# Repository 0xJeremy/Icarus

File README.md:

# Icarus Power Distribution Board

### Board Layout

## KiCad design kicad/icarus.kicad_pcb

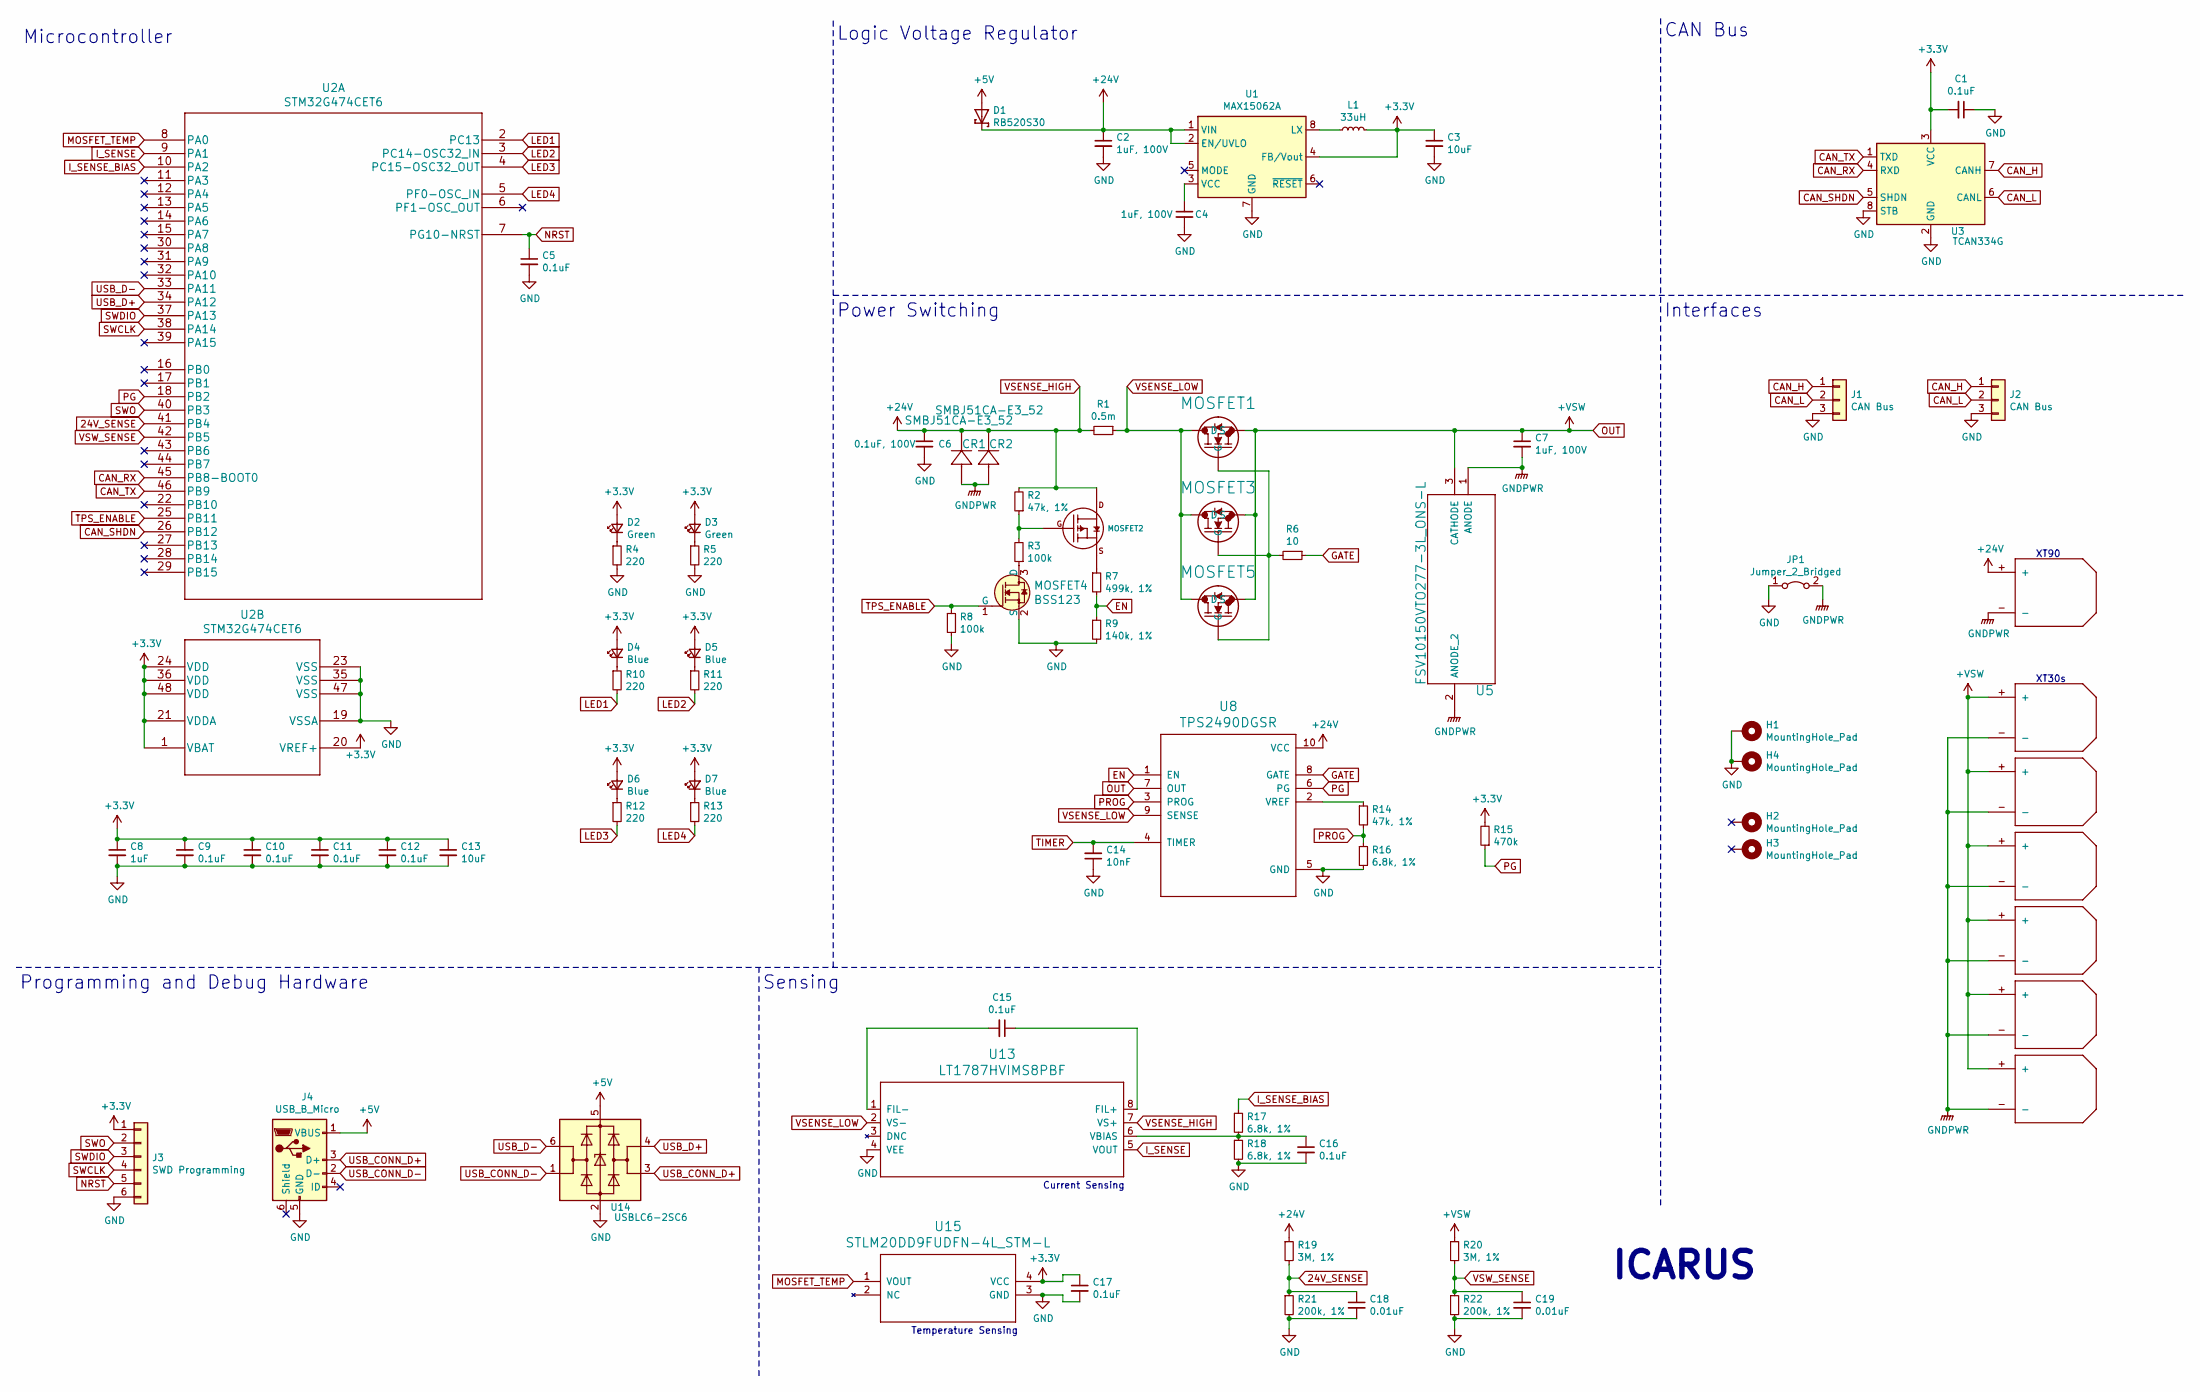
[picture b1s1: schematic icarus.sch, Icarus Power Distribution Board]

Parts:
C1, C5, C9, C10, C11, C12, C15, C16, C17: 0.1uF; C_0402_1005Metric
C2, C4, C7: 1uF, 100V; C_0805_2012Metric
C3, C13: 10uF; C_0402_1005Metric
C6: 0.1uF, 100V; C_0402_1005Metric
C8: 1uF; C_0402_1005Metric
C14: 10nF; C_0402_1005Metric
C18, C19: 0.01uF; C_0402_1005Metric
CR1, CR2: SMBJ51CA-E3_52; SMBJ51CA-E3-52
D1: RB520S30
D2, D3: Green; LED_0603_1608Metric
D4, D5, D6, D7: Blue; LED_0603_1608Metric
H1, H2, H3, H4: MountingHole_Pad; MountingHole_2.7mm_M2.5_DIN965_Pad
J1, J2: CAN Bus; JST_PH_B3B-PH-K_1x03_P2.00mm_Vertical
J3: SWD Programming; JST_PH_B6B-PH-K_1x06_P2.00mm_Vertical
J4: USB_B_Micro; USB_Micro-AB_Molex_47590-0001
JP1: Jumper_2_Bridged; SHORT_TOP-BIG
L1: 33uH; L_1210_3225Metric
MOSFET1, MOSFET3, MOSFET5: PSMN4R8-100BSEJ
MOSFET2: ZXMP10A13FTA
MOSFET4: BSS123; SOT-23-3; MPN BSS123; Digi-Key_PN BSS123NCT-ND
R1: 0.5m; R_2512_6332Metric
R2, R14: 47k, 1%; R_0402_1005Metric
R3, R8: 100k; R_0402_1005Metric
R4, R5, R10, R11, R12, R13: 220; R_0402_1005Metric
R6: 10; R_0402_1005Metric
R7: 499k, 1%; R_0402_1005Metric
R9: 140k, 1%; R_0402_1005Metric
R15: 470k; R_0402_1005Metric
R16, R17, R18: 6.8k, 1%; R_0402_1005Metric
R19, R20: 3M, 1%; R_0603_1608Metric
R21, R22: 200k, 1%; R_0402_1005Metric
U1: MAX15062A; DFN-8_2x2mm_P0.5mm
U2: STM32G474CET6
U3: TCAN334G
U4: XT90; XT90PW-M
U5: FSV10150VTO277-3L_ONS-L
U6, U7, U9, U10, U11, U12: XT30; XT30P
U8: TPS2490DGSR
U13: LT1787HVIMS8PBF
U14: USBLC6-2SC6; SOT-23-6
U15: STLM20DD9FUDFN-4L_STM-L

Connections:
24V_SENSE: C18.1, R19.2, R21.1, U2.41 (PB4)
+3V3: C1.2, C3.1, C8.1, C9.1, C10.1, C11.1, C12.1, C13.1, C17.1, D2.2 (A), D3.2 (A), D4.2 (A), D5.2 (A), D6.2 (A), D7.2 (A), J3.1, L1.2, R15.2, U1.4 (FB/Vout), U2.1 (VBAT), U2.20 (VREF+), U2.21 (VDDA), U2.24 (VDD), U2.36 (VDD), U2.48 (VDD), U3.3 (VCC), U15.4 (VCC)
+5V: D1.A, J4.1 (VBUS), U14.5 (VBUS)
CAN_H: J1.1, J2.1, U3.7 (CANH)
CAN_L: J1.2, J2.2, U3.6 (CANL)
CAN_RX: U2.45 (PB8-BOOT0), U3.4 (RXD)
CAN_SHDN: U2.26 (PB12), U3.5 (SHDN)
CAN_TX: U2.46 (PB9), U3.1 (TXD)
EN: R7.2, R9.1, U8.1 (EN)
GATE: R6.1, U8.8 (GATE)
GND: C1.1, C2.2, C3.2, C4.2, C5.2, C6.2, C8.2, C9.2, C10.2, C11.2, C12.2, C13.2, C14.1, C16.2, C17.2, C18.2, C19.2, H1.1, H4.1, J1.3, J2.3, J3.6, J4.5 (GND), JP1.1 (A), MOSFET4.2 (S), R4.2, R5.2, R8.2, R9.2, R16.2, R18.2, R21.2, R22.2, U1.7 (GND), U2.19 (VSSA), U2.23 (VSS), U2.35 (VSS), U2.47 (VSS), U3.2 (GND), U3.8 (STB), U8.5 (GND), U13.4 (VEE), U14.2 (GND), U15.3 (GND)
GNDPWR: C7.2, CR1.2, CR2.2, JP1.2 (B), U4.-, U5.1 (ANODE), U5.2 (ANODE_2), U6.-, U7.-, U9.-, U10.-, U11.-, U12.-
I_SENSE: U2.9 (PA1), U13.5 (VOUT)
I_SENSE_BIAS: R17.1, U2.10 (PA2)
LED1: R10.2, U2.2 (PC13)
LED2: R11.2, U2.3 (PC14-OSC32_IN)
LED3: R12.2, U2.4 (PC15-OSC32_OUT)
LED4: R13.2, U2.5 (PF0-OSC_IN)
MOSFET_TEMP: U2.8 (PA0), U15.1 (VOUT)
NRST: C5.1, J3.5, U2.7 (PG10-NRST)
unnamed: C4.1, U1.3 (VCC)
unnamed: C15.1, U13.8 (FIL+)
unnamed: C15.2, U13.1 (FIL-)
unnamed: C16.1, R17.2, R18.1, U13.6 (VBIAS)
unnamed: D2.1 (K), R4.1
unnamed: D3.1 (K), R5.1
unnamed: D4.1 (K), R10.1
unnamed: D5.1 (K), R11.1
unnamed: D6.1 (K), R12.1
unnamed: D7.1 (K), R13.1
unnamed: L1.1, U1.8 (LX)
unnamed: MOSFET1.1 (G), MOSFET3.1 (G), MOSFET5.1 (G), R6.2
unnamed: MOSFET2.P$1 (GATE), R2.1, R3.2
unnamed: MOSFET2.P$2 (SOURCE), R7.1
unnamed: MOSFET4.3 (D), R3.1
unnamed: R14.1, U8.2 (VREF)
OUT: C7.1, MOSFET1.3 (S), MOSFET3.3 (S), MOSFET5.3 (S), R20.1, U5.3 (CATHODE), U6.+, U7.+, U8.7 (OUT), U9.+, U10.+, U11.+, U12.+
PG: R15.1, U2.18 (PB2), U8.6 (PG)
PROG: R14.2, R16.1, U8.3 (PROG)
SWCLK: J3.4, U2.38 (PA14)
SWDIO: J3.3, U2.37 (PA13)
SWO: J3.2, U2.40 (PB3)
TIMER: C14.2, U8.4 (TIMER)
TPS_ENABLE: MOSFET4.1 (G), R8.1, U2.25 (PB11)
USB_CONN_D+: J4.3 (D+), U14.3 (I/O2)
USB_CONN_D-: J4.2 (D-), U14.1 (I/O1)
USB_D+: U2.34 (PA12), U14.4 (I/O2)
USB_D-: U2.33 (PA11), U14.6 (I/O1)
VSENSE_HIGH: C2.1, C6.1, CR1.1, CR2.1, D1.C, MOSFET2.P$3 (DRAIN), R1.2, R2.2, R19.1, U1.1 (VIN), U1.2 (EN/UVLO), U4.+, U8.10 (VCC), U13.7 (VS+)
VSENSE_LOW: MOSFET1.2 (D), MOSFET3.2 (D), MOSFET5.2 (D), R1.1, U8.9 (SENSE), U13.2 (VS-)
VSW_SENSE: C19.1, R20.2, R22.1, U2.42 (PB5)

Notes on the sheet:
ICARUS
Microcontroller
Programming and Debug Hardware
Logic Voltage Regulator
Power Switching
CAN Bus
Interfaces
Sensing
Current Sensing
Temperature Sensing
XT30s
XT90

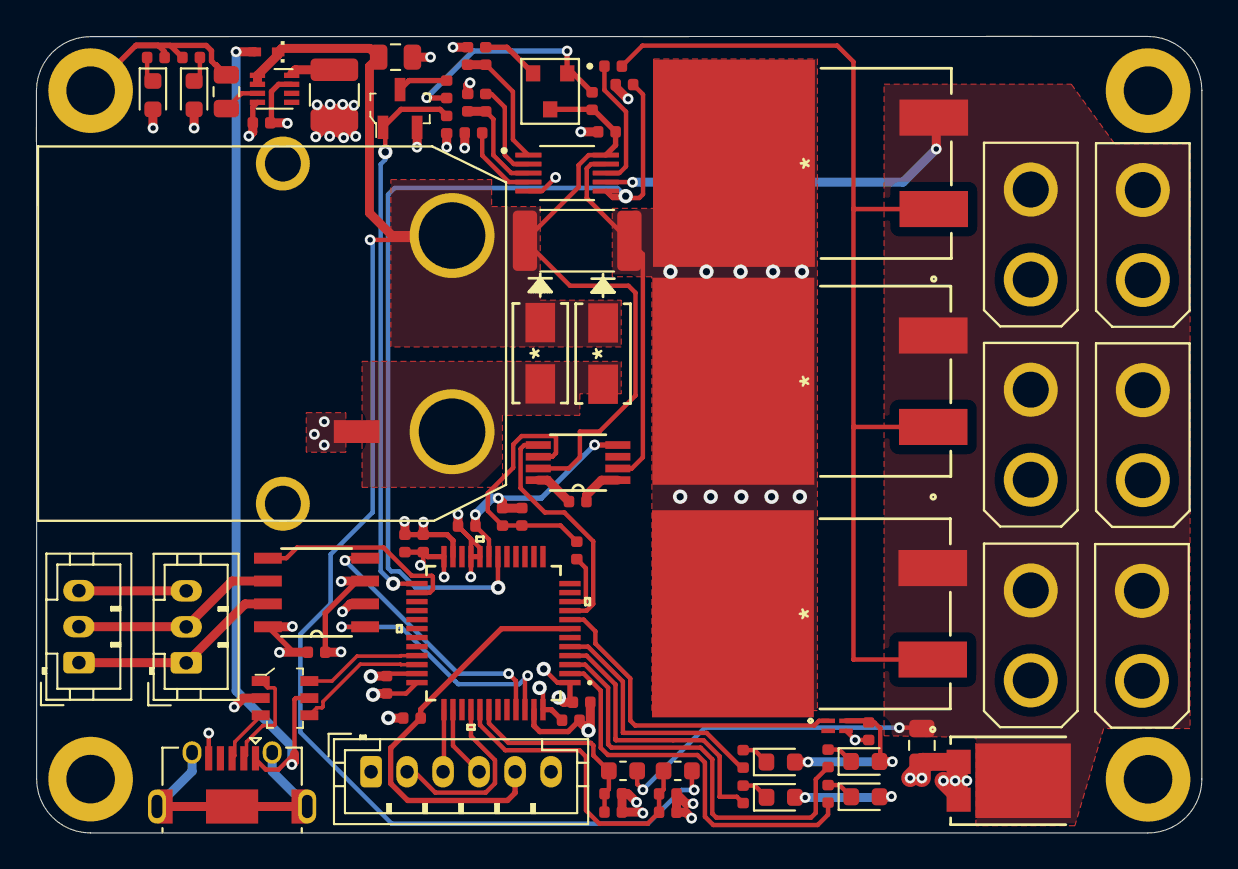
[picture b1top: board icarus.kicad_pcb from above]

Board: 4 copper layers, 64.7 x 44.2 mm, 80 parts (0 on the bottom side), 51 nets.

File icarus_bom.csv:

Reference, Quantity, Value, Footprint
C14 ,1,10nF,Capacitor_SMD:C_0402_1005Metric
C19 C18 ,2,0.01uF,Capacitor_SMD:C_0402_1005Metric
C3 C13 ,2,10uF,Capacitor_SMD:C_0402_1005Metric
C4 C2 C7 ,3,"1uF, 100V",Capacitor_SMD:C_0805_2012Metric
C6 ,1,"0.1uF, 100V",Capacitor_SMD:C_0402_1005Metric
C8 ,1,1uF,Capacitor_SMD:C_0402_1005Metric
C9 C10 C11 C1 C5 C15 C16 C17 C12 ,9,0.1uF,Capacitor_SMD:C_0402_1005Metric
CR1 CR2 ,2,SMBJ51CA-E3_52,icarus_kicad_lib:SMBJ51CA-E3-52
D1 ,1,RB520S30,icarus_kicad_lib:RB520S30
D3 D2 ,2,Green,LED_SMD:LED_0603_1608Metric
D4 D5 D6 D7 ,4,Blue,LED_SMD:LED_0603_1608Metric
H1 H2 H3 H4 ,4,MountingHole_Pad,MountingHole:MountingHole_2.7mm_M2.5_DIN965_Pad
J1 J2 ,2,CAN Bus,Connector_JST:JST_PH_B3B-PH-K_1x03_P2.00mm_Vertical
J3 ,1,SWD Programming,Connector_JST:JST_PH_B6B-PH-K_1x06_P2.00mm_Vertical
J4 ,1,USB_B_Micro,Connector_USB:USB_Micro-AB_Molex_47590-0001
JP1 ,1,Jumper_2_Bridged,icarus_kicad_lib:SHORT_TOP-BIG
L1 ,1,33uH,Inductor_SMD:L_1210_3225Metric
MOSFET1 MOSFET3 MOSFET5 ,3,PSMN4R8-100BSEJ,icarus_kicad_lib:PSMN4R8-100BSEJ
MOSFET2 ,1,ZXMP10A13FTA,icarus_kicad_lib:ZXMP10A13FTA
MOSFET4 ,1,BSS123,digikey-footprints:SOT-23-3
R1 ,1,0.5m,Resistor_SMD:R_2512_6332Metric
R14 R2 ,2,"47k, 1%",Resistor_SMD:R_0402_1005Metric
R15 ,1,470k,Resistor_SMD:R_0402_1005Metric
R16 R17 R18 ,3,"6.8k, 1%",Resistor_SMD:R_0402_1005Metric
R20 R19 ,2,"3M, 1%",Resistor_SMD:R_0603_1608Metric
R22 R21 ,2,"200k, 1%",Resistor_SMD:R_0402_1005Metric
R3 R8 ,2,100k,Resistor_SMD:R_0402_1005Metric
R5 R10 R4 R11 R12 R13 ,6,220,Resistor_SMD:R_0402_1005Metric
R6 ,1,10,Resistor_SMD:R_0402_1005Metric
R7 ,1,"499k, 1%",Resistor_SMD:R_0402_1005Metric
R9 ,1,"140k, 1%",Resistor_SMD:R_0402_1005Metric
U1 ,1,MAX15062A,Package_DFN_QFN:DFN-8_2x2mm_P0.5mm
U13 ,1,LT1787HVIMS8PBF,icarus_kicad_lib:LT1787HVIMS8PBF
U14 ,1,USBLC6-2SC6,digikey-footprints:SOT-23-6
U15 ,1,STLM20DD9FUDFN-4L_STM-L,icarus_kicad_lib:STLM20DD9FUDFN-4L_STM-L
U2 ,1,STM32G474CEU6,icarus_kicad_lib:STM32G474CEU6
U3 ,1,TCAN334G,icarus_kicad_lib:TCAN334G
U4 ,1,XT90,icarus_kicad_lib:XT90PW-M
U5 ,1,FSV10150VTO277-3L_ONS-L,icarus_kicad_lib:FSV10150VTO277-3L_ONS-L
U6 U7 U9 U10 U11 U12 ,6,XT30,icarus_kicad_lib:XT30P
U8 ,1,TPS2490DGSR,icarus_kicad_lib:TPS2490DGSR

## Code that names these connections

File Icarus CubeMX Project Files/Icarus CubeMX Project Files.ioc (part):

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PB8-BOOT0.Mode=FDCAN_Activate
Mcu.UserName=STM32G474CEUx
PC13.Signal=GPIO_Output
PA11.Mode=Device
PC14-OSC32_IN.Signal=GPIO_Output
PB11.Signal=GPIO_Output
PA13.Signal=SYS_JTMS-SWDIO
PA3.Mode=IN4-Single-Ended
PA12.Signal=USB_DP
PB9.Mode=FDCAN_Activate
PC15-OSC32_OUT.Signal=GPIO_Output
PA1.Signal=ADC1_IN2
RCC.HSE_VALUE=8000000
PB2.Signal=GPIO_Output
PB3.Mode=Trace_Asynchronous_SW
PB8-BOOT0.Signal=FDCAN1_RX
board=custom
PA1.Mode=IN2-Single-Ended
PA14.Mode=Trace_Asynchronous_SW
PA0.Mode=IN1-Single-Ended
PA13.Mode=Trace_Asynchronous_SW
Mcu.Name=STM32G474C(B-C-E)Ux
PA2.Signal=ADC1_IN3
PA0.Signal=ADC1_IN1
PB3.Signal=SYS_JTDO-SWO
RCC.SYSCLKFreq_VALUE=16000000
Mcu.Package=UFQFPN48
PB5.Signal=GPIO_Input
PB9.Signal=FDCAN1_TX
PA12.Mode=Device
PA11.Signal=USB_DM
PA14.Signal=SYS_JTCK-SWCLK
PA2.Mode=IN3-Single-Ended
PF0-OSC_IN.Signal=GPIO_Output
PB12.Signal=GPIO_Output
PB4.Signal=GPIO_Input
PA3.Signal=ADC1_IN4

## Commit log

2021-03-05 Added README
2021-03-05 Added Icarus Logo
2021-03-05 Began Icarus schematic, added CubeMX files
2021-03-05 Added schematic symbols, continued schematic layout
2021-03-06 Added voltage sensing
2021-03-06 Added mosfets to power driver enable, added parts values
2021-03-07 Updated schematic and CubeMX pinouts
2021-03-07 Added initial BOM
2021-03-07 Added and assigned footprints, generated netlist
2021-03-07 Began fixing footprint disasters:
2021-03-07 Finished importing and modifying footprints
2021-03-07 Initial rough layout done
2021-03-07 Compressed board layout, about to start traces
2021-03-08 Began initial routing
2021-03-09 Added ground plane, adjusted schematic
2021-03-09 Layout v1.0 done
2021-03-11 Updated BOM, updated layout to fix design rules
2021-03-11 Updated BOM
2021-03-15 Updated PCB layout
2021-03-15 Added Icarus BMP Logo
2021-03-15 Added gerber and assembly files
2021-03-17 Changed MCU due to sourcing problems
2021-03-31 Updated 3D model
2021-03-31 Added renders
2021-05-07 Added full position file, added images
2021-05-09 Updated readme and logo
2021-06-15 Added .step model
